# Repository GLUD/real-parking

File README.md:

# real-parking
Proyecto de Software y Hardware que pretente mejorar la movilidad de los parqueaderos a partir del análisis de datos.

Es un sistema escalable de parqueaderos. Busca ver toda la ciudad como un gran parqueadero y ayuda a gestionar de mejor manera el recurso espacial. Tiene un incentivo de gamificación con lo cuál se premia fidelidad a un parqueadero, entre otras cosas. Tiene un módulo de recomendaciones que dice cuál es el parqueadero mejor en relación precio/distancia del destino.

### INFORMACIÓN DE CONTACTO DESARROLLADORES ###

* Desarrollador: Jorge Ulises Useche Cuellar   
Ingeniero Electónico de la Udistrital FJC  
Movil: 3114813719  
Twitter: @juusechec   
LinkedIn: https://co.linkedin.com/in/juusechec  

* Desarrollador: Diego Javier Mena Amado  
Ingeniero Electrónico de la UDistrital FJC  
Movil: 3133067541  
Twitter: @DiegoJavierMena  
LinkedIn: https://www.linkedin.com/in/diego-javier-mena-amado-3357a873/en

* Desarrollador: Andrés Angarita  
Ingeniero de Sistemas de la UDistrital FJC  
Movil:   
Twitter: @   
LinkedIn:   

* Desarrollador: David Castelblanco  
Ingeniero de Sistemas de la UDistrital FJC  
Movil:   
Twitter: @   
LinkedIn:  

### Material de Presentación ###

https://www.youtube.com/watch?v=H8S8lVXx5Ek

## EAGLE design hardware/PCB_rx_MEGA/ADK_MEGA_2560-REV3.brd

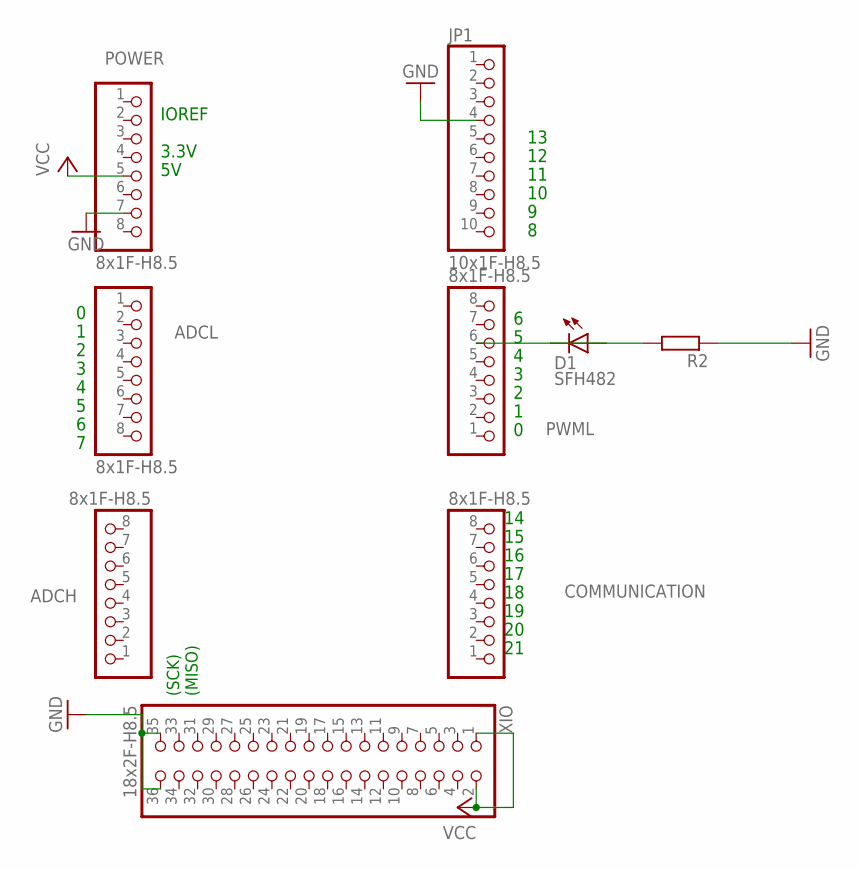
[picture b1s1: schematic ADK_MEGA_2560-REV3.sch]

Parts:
ADCH: 8x1F-H8.5; 1X08
ADCL: 8x1F-H8.5; 1X08
COMMUNICATION: 8x1F-H8.5; 1X08
D1: SFH482
JP1: 10x1F-H8.5; 1X10
POWER: 8x1F-H8.5; 1X08
PWML: 8x1F-H8.5; 1X08
R2: R0204/7; 0204/7
XIO: 18x2F-H8.5; 2X18

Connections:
GND: JP1.4, POWER.7, R2.1, XIO.35, XIO.36
unnamed: D1.K (C), PWML.6
unnamed: D1.A, R2.2
VCC: POWER.5, XIO.1, XIO.2

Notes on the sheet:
(SCK)
(MISO)
IOREF
3.3V

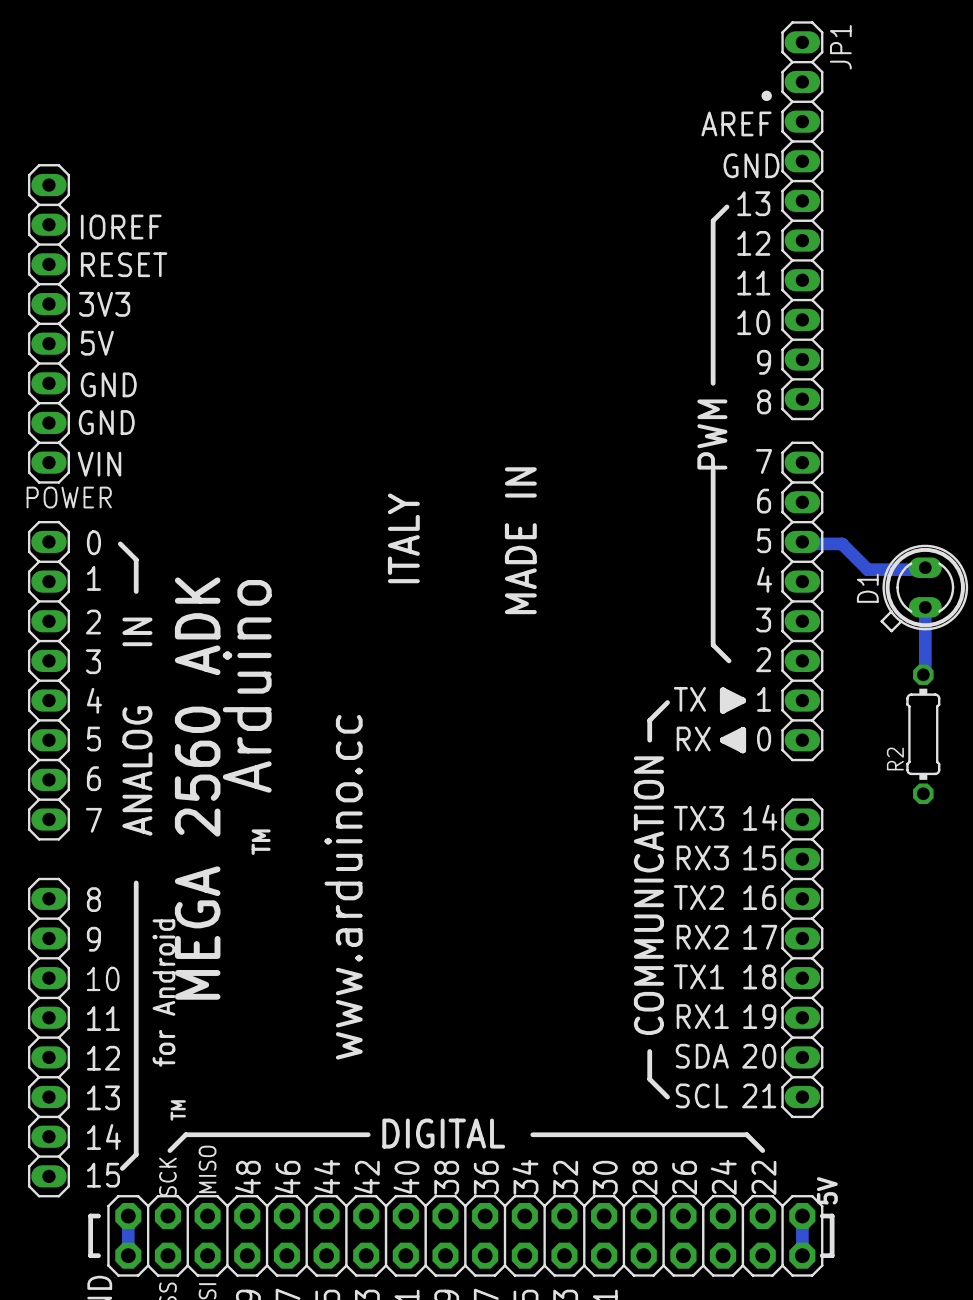
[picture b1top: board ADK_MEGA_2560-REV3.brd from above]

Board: 2 copper layers, 9 parts (0 on the bottom side), 4 nets.

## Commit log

2016-11-12 Se crea el archivo package.json, y se instalan algunas dependencias
2016-11-12 Se crea emisor de eventos básico
2016-11-12 Se empieza la implementación del index del proyecto, y el servidor de los sockets
2016-11-12 código inicial del emisor y transmisor
2016-11-12 Se cargan las rutas dinámicamente
2016-11-12 Se empezo a implementar el modulo que se comunica con el nodo central del parqueadero
2016-11-12 Se añade algoritmo para la recepcion de tiempo generado por el transmisor
2016-11-12 Se transmite un dato time
2016-11-12 Se añade algoritmo para la detección de vehiculos con ultrasonido
2016-11-12 Se implementa un proxy inverso para resolver problemas de cors con el geoServer
2016-11-12 Se implementa visor geográfico
2016-11-12 Se crea evento para seleccionar una isla, y cambiar su estado
2016-11-12 Se implemento la funcionalidad de tiempo real, para notificar al cliente cuando un vehiculo ingresa a una isla, o la abandona
2016-11-12 Se organizan las dependencias del package.json, y se crea un script de construcción
2016-11-12 se documenta
2016-11-12 Se crea el componente visual, que se encarga de gestionar los cobros
2016-11-12 Se suben los cambios de archivos miscelaneos
2016-11-12 código inicial
2016-11-13 Se agrega código de sleep ArduinoMega, 20mA de Ahorro
2016-11-13 Se implementan end points del API para actualizar, y consultar registros
2016-11-13 Parte del API relacionada con consultas, y su respectiva comunicación desde el cliente
2016-11-13 Nodo Central presuntamente terminado
2016-11-13 Se implementa la funcionalidad del modelo en la vista de cobro, se utiliza una libreria para emitir eventos
2016-11-13 Se instala, y se integra el middleware body-parser
2016-11-13 Se implementa el modulo de la base de datos
2016-11-13 Logos
2016-11-13 Se implementa un metodo para buscar registros por id, y se crea una interfaz, que controla el número de instancias de la base de datos
2016-11-13 Se usa la implementación de la base de datos para almacenar y actualizar información
2016-11-13 Se corrigen algunos errores en el cliente
2016-11-13 Cambios menores
2016-11-13 Se envían datos de Ejemplo de Id Isla y Estado Isla (ocupado, vacio, baja bateria)
2016-11-13 Nodo centrar recibe 2 bytes de información sobre estado e isla
2016-11-13 Leer isla y su estado
2016-11-13 Se hacen algunos ajustes en el código
2016-11-13 Se implementa codigo Ultrasonido
2016-11-13 Isla 1 terminada
2016-11-13 se añade esquematico en fritzing para ilsa-emisor
2016-11-13 Se integran dos islas al nodo central-receptor
2016-11-13 Se realizan peticiones repetitivas
2016-11-13 Código del sensor de isla 2 con interruptor como cambio de estado
2016-11-14 Se agregan animaciones
2016-11-14 Se agrega imagenes de diapositivas
2016-11-22 Se añade diseño PCB en Eagle del prototipo-receptor
2016-11-27 Se arregla diseño PCB del modulo transmisor
2016-11-29 Se añade PCB_rx_MEGA
2016-11-29 Se añade modulo de comunicaciones junto con regulador al diseño de la shield para el nodo central
